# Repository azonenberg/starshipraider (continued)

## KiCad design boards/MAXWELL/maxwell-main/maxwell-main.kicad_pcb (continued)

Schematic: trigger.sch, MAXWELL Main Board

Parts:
C203: 1 uF; EIA_0603_CAP_NOSILK
C205, C206, C207, C208, C209, C210: 4.7 uF; EIA_0603_CAP_NOSILK
C211, C212, C213, C214, C215, C216, C217, C218, C219, C220, C221, C222, C224, C225, C226, C227: 0.47 uF; EIA_0402_CAP_NOSILK
C223: 0.1 uF; EIA_0402_CAP_NOSILK
C228: 0.01 uF; EIA_0402_CAP_NOSILK
J12, J13, J14, J21, J22, J23, J25: 901-10511-3; CONN_SMA_EDGE_AMPHENOL_901_10511_3
R70, R71, R72: PAT1220-C-6DB-T5; EIA_0805_PI_ATTENUATOR
R73, R74, R75: 4.99K; EIA_0402_RES_NOSILK
R77, R78, R79, R80, R81, R82: 10K; EIA_0402_RES_NOSILK
R90, R91, R93: 49.9; EIA_0402_RES_NOSILK
R125, R126, R127, R128, R129, R130: 62; EIA_0402_RES_NOSILK
R133, R134, R135, R136, R137, R138: 240; EIA_0402_RES_NOSILK
TP45, TP46, TP47, TP48: TESTCLIP; TESTPOINT_SMT_KEYSTONE_5016
U37, U38: LMH7322; QFN_24_0.5MM_4x4MM
U40: SY89835U; DFN_8_0.5MM_2x2MM
U41, U42, U43, U44, U85: RCLAMP0542T; DFN_6_0.5MM_1.6x1.0MM

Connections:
/2V5: C207.1, C210.1, C213.1, C214.1, C217.1, C218.1, C221.1, C222.1, C223.1, C226.1, C227.1, C228.1, R78.1, R80.1, R82.1, R133.1, R134.1, R135.1, R136.1, R137.1, R138.1, TP48.1, U37.1 (VCCO), U37.18 (VCCO), U37.21 (VCCO), U37.22 (VCCO), U38.1 (VCCO), U38.22 (VCCO), U40.1 (VCC); also elsewhere on the board
/5V0: C205.1, C208.1, C211.1, C215.1, C219.1, C224.1, TP46.1, U37.5 (VCCI), U37.14 (VCCI), U38.5 (VCCI); also elsewhere on the board
/5V0_N: C206.1, C209.1, C212.1, C216.1, C220.1, C225.1, R77.1, R79.1, R81.1, TP47.1, U37.4 (VSS), U37.15 (VSS), U37.PAD, U38.4 (VSS), U38.PAD; also elsewhere on the board
/Clocking/EXT_TRIG_1_N: U40.7 (Q0_N); also elsewhere on the board
/Clocking/EXT_TRIG_1_P: U40.8 (Q0_P); also elsewhere on the board
/Clocking/EXT_TRIG_2_N: U40.5 (Q1_N); also elsewhere on the board
/Clocking/EXT_TRIG_2_P: U40.6 (Q1_P); also elsewhere on the board
/Clocking/REF_IN_N: R128.1, R136.2, U38.24 (Q_N); also elsewhere on the board
/Clocking/REF_IN_P: R127.1, R135.2, U38.23 (Q_P); also elsewhere on the board
/Clocking/REF_OUT: J23.1 (In), U44.1 (LINE_1), U44.6 (NC_1); also elsewhere on the board
/Clocking/REF_OUT_N: J21.1 (In), U43.1 (LINE_1), U43.6 (NC_1); also elsewhere on the board
/Clocking/REF_OUT_P: J22.1 (In), U43.2 (LINE_2), U43.5 (NC_2); also elsewhere on the board
/Clocking/TRIG_OUT_MUX_P: J25.1 (In), U85.1 (LINE_1), U85.6 (NC_1); also elsewhere on the board
/Clocking/Trigger and Reference Inputs/PPS_IN: J14.1 (In), R72.1 (RF_IN)
/Clocking/Trigger and Reference Inputs/PPS_IN_ATTEN: R72.2 (RF_OUT), R91.1, U37.8 (IN_P), U42.1 (LINE_1), U42.6 (NC_1)
/Clocking/Trigger and Reference Inputs/REFCLK_IN: J13.1 (In), R71.1 (RF_IN)
/Clocking/Trigger and Reference Inputs/REF_IN_AC: C203.1, R93.1, U38.8 (IN_P)
/Clocking/Trigger and Reference Inputs/REF_IN_ATTEN: C203.2, R71.2 (RF_OUT), U41.2 (LINE_2), U41.5 (NC_2)
/Clocking/Trigger and Reference Inputs/TRIG_IN: J12.1 (In), R70.1 (RF_IN)
/Clocking/Trigger and Reference Inputs/TRIG_IN_ATTEN: R70.2 (RF_OUT), R90.1, U37.11 (IN_P), U42.2 (LINE_2), U42.5 (NC_2)
/Clocking/Trigger and Reference Inputs/TRIG_IN_N: R126.1, R134.2, U37.19 (Q_N), U40.3 (IN_N)
/Clocking/Trigger and Reference Inputs/TRIG_IN_P: R125.1, R133.2, U37.20 (Q_P), U40.2 (IN_P)
/GND: C205.2, C206.2, C207.2, C208.2, C209.2, C210.2, C211.2, C212.2, C213.2, C214.2, C215.2, C216.2, C217.2, C218.2, C219.2, C220.2, C221.2, C222.2, C223.2, C224.2, C225.2, C226.2, C227.2, C228.2, J12.2 (Ext), J13.2 (Ext), J14.2 (Ext), J21.2 (Ext), J22.2 (Ext), J23.2 (Ext), J25.2 (Ext), R70.3 (GND), R71.3 (GND), R72.3 (GND), R90.2, R91.2, R93.2, R125.2, R126.2, R127.2, R128.2, R129.2, R130.2, TP45.1, U37.7 (IN_N), U37.12 (IN_N), U38.7 (IN_N), U40.4 (GND), U40.PAD (GND), U41.3 (Gnd), U41.4 (Gnd), U42.3 (Gnd), U42.4 (Gnd), U43.3 (Gnd), U43.4 (Gnd), U44.3 (Gnd), U44.4 (Gnd), U85.3 (Gnd), U85.4 (Gnd); also elsewhere on the board
/PPS_IN_N: R130.1, R138.2, U37.24 (Q_N); also elsewhere on the board
/PPS_IN_P: R129.1, R137.2, U37.23 (Q_P); also elsewhere on the board
unnamed: R73.1, U37.13 (RHYS)
unnamed: R73.2, U37.10 (RHREF)
unnamed: R74.1, U38.6 (RHYS)
unnamed: R74.2, U38.9 (RHREF)
unnamed: R75.1, U37.6 (RHYS)
unnamed: R75.2, U37.9 (RHREF)
unnamed: R77.2, U37.17 (LE_P)
unnamed: R78.2, U37.16 (LE_N)
unnamed: R79.2, U38.2 (LE_P)
unnamed: R80.2, U38.3 (LE_N)
unnamed: R81.2, U37.2 (LE_P)
unnamed: R82.2, U37.3 (LE_N)

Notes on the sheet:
PECL load resistors
Attenuator power limit is +21.25 dBm or ~~7V p-p Rate the input for +20 dBm max to provide some safety margin. Comparator starts slowing down around +/- 20 mV overdrive. This is +/- 40 mV before the attenuator or about -18 dBm.
20 mV hysteresis
Comparator decoupling

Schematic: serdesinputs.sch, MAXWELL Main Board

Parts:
C65, C66, C67, C68, C81, C82, C89, C90, C355, C356, C357, C358, C365, C366, C367, C368: 1 uF; EIA_0603_CAP_NOSILK
C69, C70, C75, C76, C85, C86, C93, C94, C99, C100, C109, C110, C269, C270: 0.1 uF; EIA_0402_CAP_NOSILK
C71, C72, C73, C74, C77, C78, C79, C80, C83, C84, C87, C88, C91, C92, C95, C96, C107, C108, C111, C112, C351, C352, C353, C354, C359, C360, C361, C362, C363, C364, C369, C370, C371, C372, C373, C374: 0.01 uF; EIA_0402_CAP_NOSILK
C440, C441, C442, C443, C444, C445, C446, C447: 0.47 uF; EIA_0402_CAP_NOSILK
R85, R86, R87, R88: 220; EIA_0402_RES_NOSILK
R142, R145, R148, R183: DNP; EIA_0402_RES_NOSILK
R143, R144, R146, R147, R149, R182, R184, R185: 750; EIA_0402_RES_NOSILK
U2: XC7K160T-2FFG676C; BGA_676_27x27_FULLARRAY_1MM_FFG676
U30, U31, U32, U33: SY56017R; QFN_16_0.5MM_3x3MM
U48, U49, U50, U51: ADCMP582; QFN_16_0.5MM_3x3MM

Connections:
/0V5: C68.1, C78.1, C90.1, C352.1, C358.1, C362.1, C368.1, C372.1, C440.1, C441.1, C444.1, C445.1, U30.2 (VT0), U31.2 (VT0), U32.2 (VT0), U33.2 (VT0), U48.1 (VT_P), U48.4 (VT_N), U48.8 (VCCO_VTT), U49.1 (VT_P), U49.4 (VT_N), U49.8 (VCCO_VTT), U50.1 (VT_P), U50.4 (VT_N), U50.8 (VCCO_VTT), U51.1 (VT_P), U51.4 (VT_N), U51.8 (VCCO_VTT); also elsewhere on the board
/1V2: C75.1, C76.1, C83.1, C84.1, C85.1, C86.1, C87.1, C88.1, C99.1, C100.1, C107.1, C108.1, C109.1, C110.1, C111.1, C112.1, U30.8 (VCCO), U30.13 (VCCO), U31.8 (VCCO), U31.13 (VCCO), U32.8 (VCCO), U32.13 (VCCO), U33.8 (VCCO), U33.13 (VCCO); also elsewhere on the board
/2V5: C67.1, C69.1, C70.1, C71.1, C72.1, C77.1, C80.1, C89.1, C93.1, C94.1, C95.1, C96.1, C351.1, C354.1, C357.1, C361.1, C364.1, C367.1, C371.1, C374.1, C442.1, C443.1, C446.1, C447.1, R85.1, R87.1, R143.1, R146.1, R149.1, R184.1, U30.3 (VT1), U30.7 (VCC), U31.3 (VT1), U31.7 (VCC), U32.3 (VT1), U32.7 (VCC), U33.3 (VT1), U33.7 (VCC), U48.9 (VCCO), U48.12 (VCCO), U49.9 (VCCO), U49.12 (VCCO), U50.9 (VCCO), U50.12 (VCCO), U51.9 (VCCO), U51.12 (VCCO); also elsewhere on the board
/5V0: C65.1, C73.1, C79.1, C81.1, C91.1, C353.1, C355.1, C359.1, C363.1, C365.1, C369.1, C373.1, U48.5 (VCCI), U48.16 (VCCI), U49.5 (VCCI), U49.16 (VCCI), U50.5 (VCCI), U50.16 (VCCI), U51.5 (VCCI), U51.16 (VCCI); also elsewhere on the board
/5V0_N: C66.1, C74.1, C82.1, C92.1, C356.1, C360.1, C366.1, C370.1, R142.1, R145.1, R148.1, R183.1, U48.13 (VEE), U49.13 (VEE), U50.13 (VEE), U51.13 (VEE); also elsewhere on the board
/Clocking/EXT_TRIG_1_N: U30.5 (IN1_N); also elsewhere on the board
/Clocking/EXT_TRIG_1_P: U30.4 (IN1_P); also elsewhere on the board
/Clocking/GTX_TRIG_OUT_N: U2.F1 (MGTXTXN0_116); also elsewhere on the board
/Clocking/GTX_TRIG_OUT_P: U2.F2 (MGTXTXP0_116); also elsewhere on the board
/Clocking/LA_REFCLK_N: C270.2; also elsewhere on the board
/Clocking/LA_REFCLK_P: C269.2; also elsewhere on the board
/Clocking/SYNC_CLK_1_N: U31.5 (IN1_N); also elsewhere on the board
/Clocking/SYNC_CLK_1_P: U31.4 (IN1_P); also elsewhere on the board
/GND: C65.2, C66.2, C67.2, C68.2, C69.2, C70.2, C71.2, C72.2, C73.2, C74.2, C75.2, C76.2, C77.2, C78.2, C79.2, C80.2, C81.2, C82.2, C83.2, C84.2, C85.2, C86.2, C87.2, C88.2, C89.2, C90.2, C91.2, C92.2, C93.2, C94.2, C95.2, C96.2, C99.2, C100.2, C107.2, C108.2, C109.2, C110.2, C111.2, C112.2, C351.2, C352.2, C353.2, C354.2, C355.2, C356.2, C357.2, C358.2, C359.2, C360.2, C361.2, C362.2, C363.2, C364.2, C365.2, C366.2, C367.2, C368.2, C369.2, C370.2, C371.2, C372.2, C373.2, C374.2, C440.2, C441.2, C442.2, C443.2, C444.2, C445.2, C446.2, C447.2, R86.1, R88.1, R144.1, R147.1, R182.1, R185.1, U30.14 (GND), U30.PAD (GND), U31.14 (GND), U31.PAD (GND), U32.14 (GND), U32.PAD (GND), U33.14 (GND), U33.PAD (GND), U48.15 (GND), U49.15 (GND), U50.15 (GND), U51.15 (GND); also elsewhere on the board
/Inputs/Right Pods/MUX0_EQ: U30.6 (EQ); also elsewhere on the board
/Inputs/Right Pods/MUX0_SEL: U30.15 (SEL); also elsewhere on the board
/Inputs/Right Pods/MUX1_EQ: U31.6 (EQ); also elsewhere on the board
/Inputs/Right Pods/MUX1_SEL: U31.15 (SEL); also elsewhere on the board
/Inputs/Right Pods/MUX2_EQ: U32.6 (EQ); also elsewhere on the board
/Inputs/Right Pods/MUX2_SEL: U32.15 (SEL); also elsewhere on the board
/Inputs/Right Pods/MUX3_EQ: U33.6 (EQ); also elsewhere on the board
/Inputs/Right Pods/MUX3_SEL: U33.15 (SEL); also elsewhere on the board
/Inputs/Right Pods/POD11_D4_N: U48.2 (VIN_P); also elsewhere on the board
/Inputs/Right Pods/POD11_D4_P: U48.3 (VIN_N); also elsewhere on the board
/Inputs/Right Pods/POD11_D5_N: U49.2 (VIN_P); also elsewhere on the board
/Inputs/Right Pods/POD11_D5_P: U49.3 (VIN_N); also elsewhere on the board
/Inputs/Right Pods/POD11_D6_N: U50.2 (VIN_P); also elsewhere on the board
/Inputs/Right Pods/POD11_D6_P: U50.3 (VIN_N); also elsewhere on the board
/Inputs/Right Pods/POD11_D7_N: U51.2 (VIN_P); also elsewhere on the board
/Inputs/Right Pods/POD11_D7_P: U51.3 (VIN_N); also elsewhere on the board
/Inputs/Right Pods/SERDES inputs/CH0_N: U2.G3 (MGTXRXN0_116), U30.10 (Q_N)
/Inputs/Right Pods/SERDES inputs/CH0_P: U2.G4 (MGTXRXP0_116), U30.11 (Q_P)
/Inputs/Right Pods/SERDES inputs/CH1_N: U2.E3 (MGTXRXN1_116), U31.10 (Q_N)
/Inputs/Right Pods/SERDES inputs/CH1_P: U2.E4 (MGTXRXP1_116), U31.11 (Q_P)
/Inputs/Right Pods/SERDES inputs/CH2_N: U2.C3 (MGTXRXN2_116), U32.10 (Q_N)
/Inputs/Right Pods/SERDES inputs/CH2_P: U2.C4 (MGTXRXP2_116), U32.11 (Q_P)
/Inputs/Right Pods/SERDES inputs/CH3_N: U2.B5 (MGTXRXN3_116), U33.10 (Q_N)
/Inputs/Right Pods/SERDES inputs/CH3_P: U2.B6 (MGTXRXP3_116), U33.11 (Q_P)
/Inputs/Right Pods/SERDES inputs/IN0_BUF_N: U30.1 (IN0_N), U48.11 (Q_P)
/Inputs/Right Pods/SERDES inputs/IN0_BUF_P: U30.16 (IN0_P), U48.10 (Q_N)
/Inputs/Right Pods/SERDES inputs/IN1_BUF_N: U31.1 (IN0_N), U49.11 (Q_P)
/Inputs/Right Pods/SERDES inputs/IN1_BUF_P: U31.16 (IN0_P), U49.10 (Q_N)
/Inputs/Right Pods/SERDES inputs/IN2_BUF_N: U32.1 (IN0_N), U50.11 (Q_P)
/Inputs/Right Pods/SERDES inputs/IN2_BUF_P: U32.16 (IN0_P), U50.10 (Q_N)
/Inputs/Right Pods/SERDES inputs/IN3_BUF_N: U33.1 (IN0_N), U51.11 (Q_P)
/Inputs/Right Pods/SERDES inputs/IN3_BUF_P: U33.16 (IN0_P), U51.10 (Q_N)
/Inputs/Right Pods/SERDES inputs/REFCLK_AC_N: C270.1, U2.D5 (MGTREFCLK0N_116)
/Inputs/Right Pods/SERDES inputs/REFCLK_AC_P: C269.1, U2.D6 (MGTREFCLK0P_116)
/Inputs/Right Pods/SERDES inputs/UNUSED1_N: R86.2, U32.5 (IN1_N)
/Inputs/Right Pods/SERDES inputs/UNUSED1_P: R85.2, U32.4 (IN1_P)
/Inputs/Right Pods/SERDES inputs/UNUSED2_N: R88.2, U33.5 (IN1_N)
/Inputs/Right Pods/SERDES inputs/UNUSED2_P: R87.2, U33.4 (IN1_P)
unnamed: R142.2, U48.14 (VHYS)
unnamed: R143.2, U48.7 (LE_P)
unnamed: R144.2, U48.6 (LE_N)
unnamed: R145.2, U49.14 (VHYS)
unnamed: R146.2, U49.7 (LE_P)
unnamed: R147.2, U49.6 (LE_N)
unnamed: R148.2, U50.14 (VHYS)
unnamed: R149.2, U50.7 (LE_P)
unnamed: R182.2, U50.6 (LE_N)
unnamed: R183.2, U51.14 (VHYS)
unnamed: R184.2, U51.7 (LE_P)
unnamed: R185.2, U51.6 (LE_N)

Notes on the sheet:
Tie unused inputs to constant value so they don't oscillate
SY56017 @ VCCO=1V2 Output swing 780 mV differential below 1V2 Input 400 - 2000 mV Input to Vt max 1280 mV GTX: inputs terminated with 50 ohms per leg to Avtt SE input range -200 to +1200 mV Input voltage 150 to 1250 differential

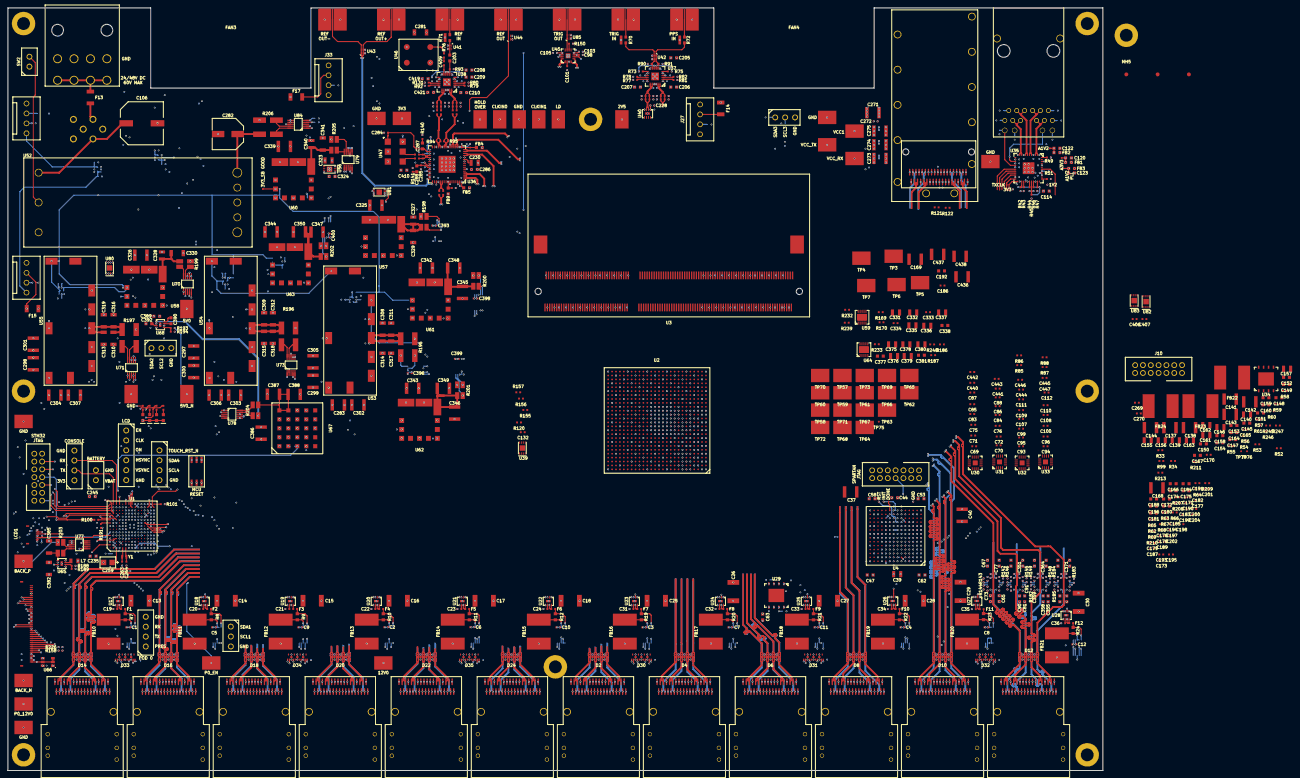
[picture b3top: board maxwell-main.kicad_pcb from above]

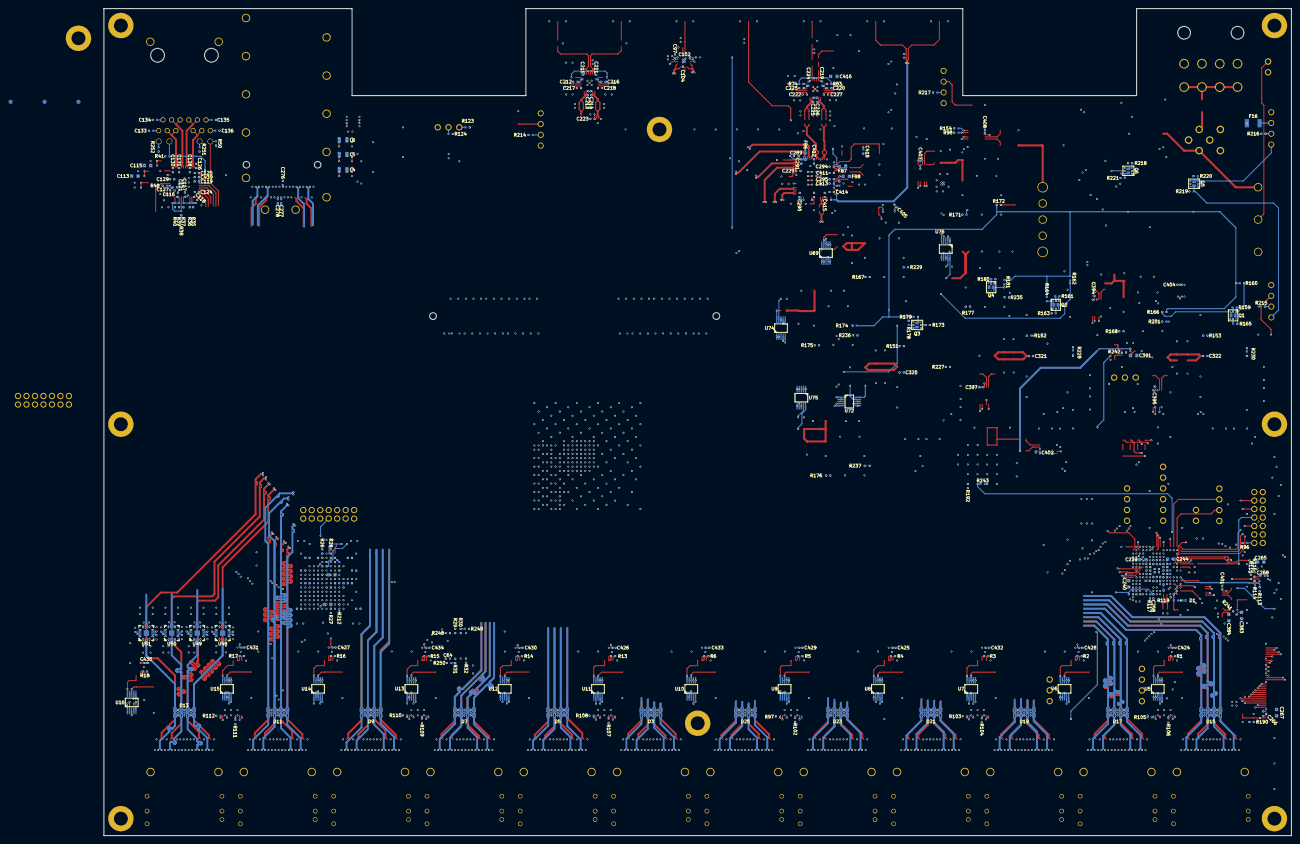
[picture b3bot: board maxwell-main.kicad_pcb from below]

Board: 8 copper layers, 280.0 x 195.0 mm, 996 parts (290 on the bottom side), 921 nets.

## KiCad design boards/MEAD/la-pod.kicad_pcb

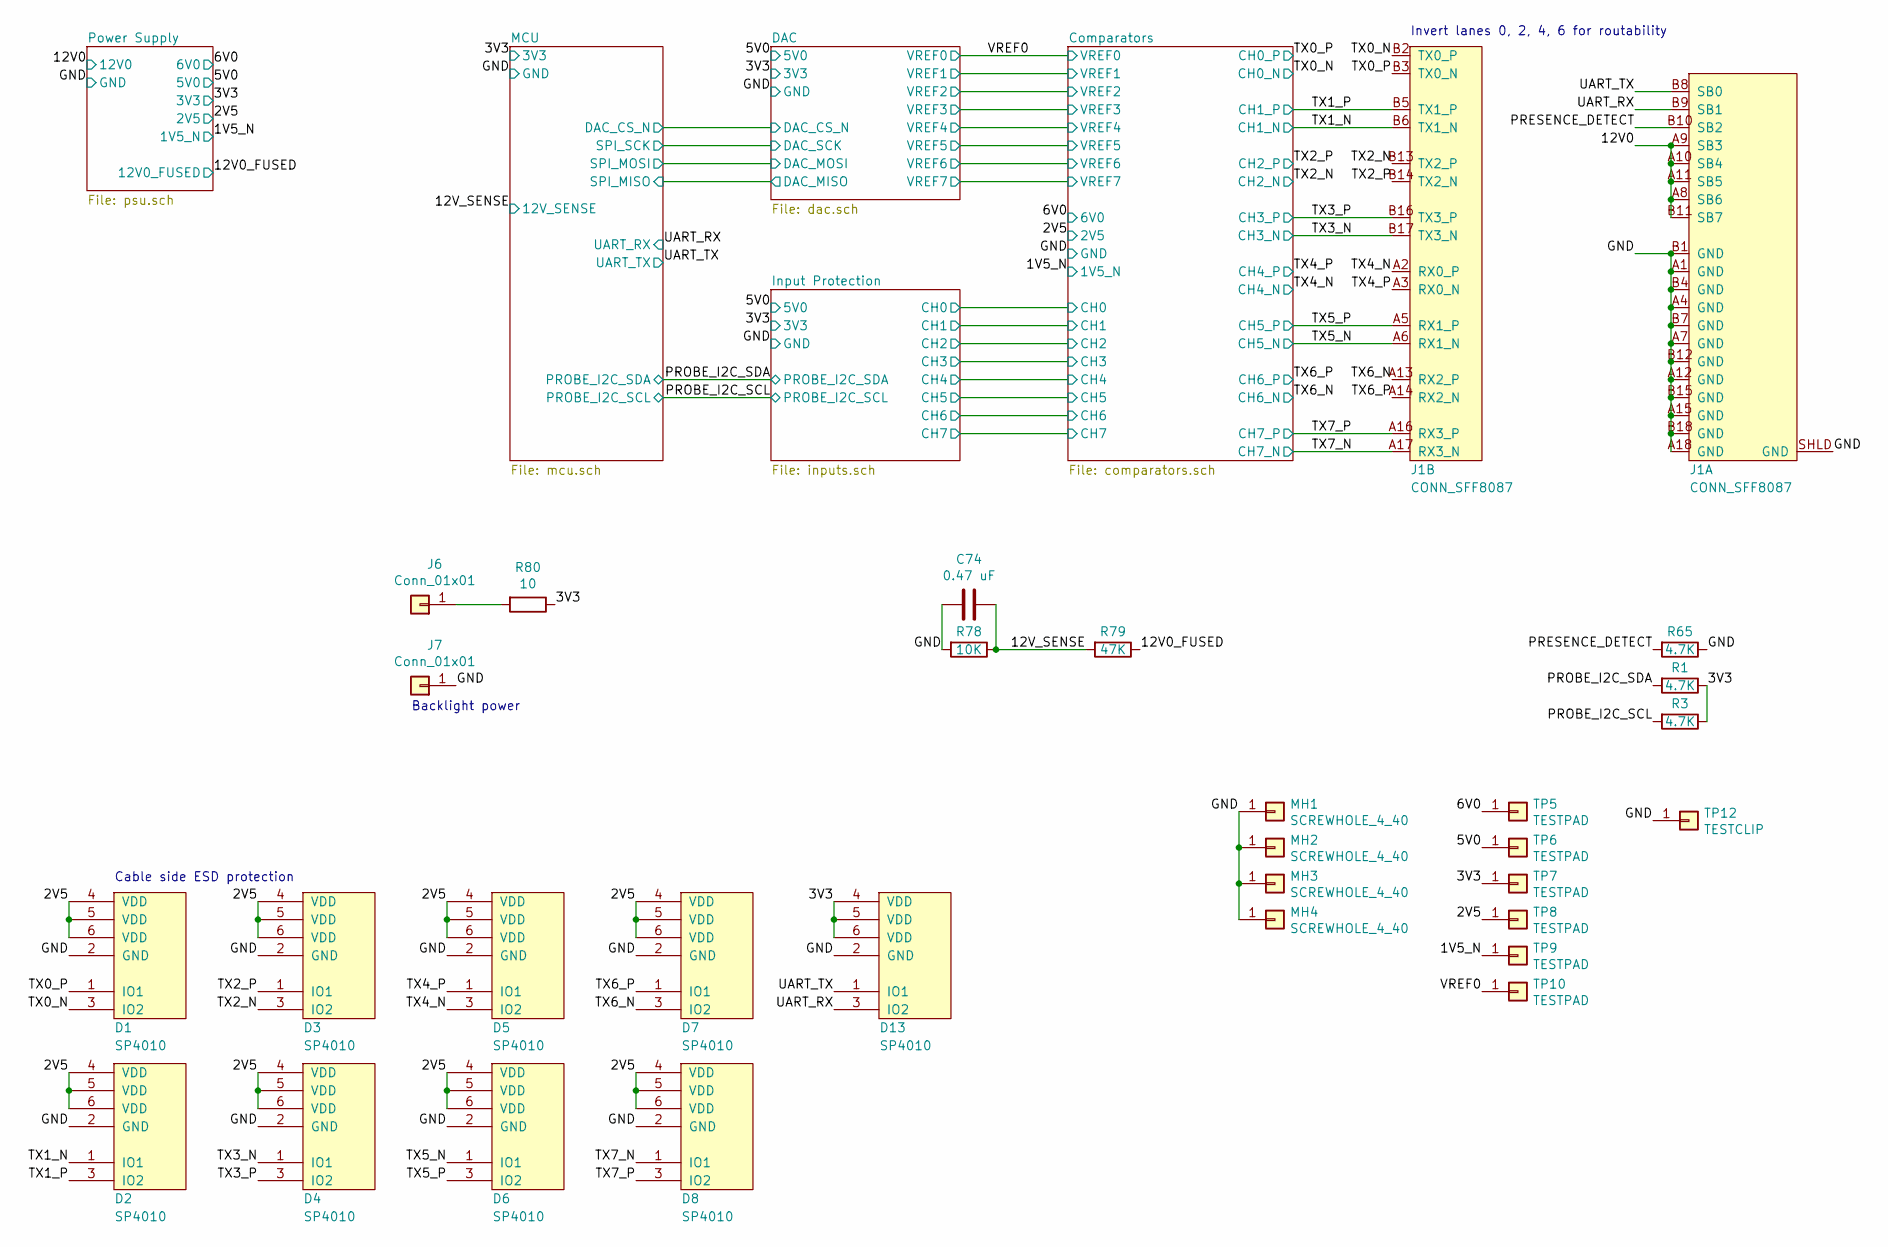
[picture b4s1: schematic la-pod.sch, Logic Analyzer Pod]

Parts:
C74: 0.47 uF; EIA_0402_CAP_NOSILK
D1, D2, D3, D4, D5, D6, D7, D8, D13: SP4010; SOT23_6
J1: CONN_SFF8087; CONN_SFF8087_MOLEX_75783-0140
J6, J7: Conn_01x01; CONN_HEADER_2.54MM_1x1
MH1, MH2, MH3, MH4: SCREWHOLE_4_40; MECHANICAL_CLEARANCEHOLE_4_40
R1, R3, R65: 4.7K; EIA_0402_RES_NOSILK
R78: 10K; EIA_0402_RES_NOSILK
R79: 47K; EIA_0402_RES_NOSILK
R80: 10; EIA_0805_CAP_NOSILK
TP5, TP6, TP7, TP8, TP9, TP10: TESTPAD; TESTPOINT_SMT_0.5MM
TP12: TESTCLIP; TESTPOINT_SMT_KEYSTONE_5016

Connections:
/1V5_N: TP9.1; also elsewhere on the board
/2V5: D1.4 (VDD), D1.5 (VDD), D1.6 (VDD), D2.4 (VDD), D2.5 (VDD), D2.6 (VDD), D3.4 (VDD), D3.5 (VDD), D3.6 (VDD), D4.4 (VDD), D4.5 (VDD), D4.6 (VDD), D5.4 (VDD), D5.5 (VDD), D5.6 (VDD), D6.4 (VDD), D6.5 (VDD), D6.6 (VDD), D7.4 (VDD), D7.5 (VDD), D7.6 (VDD), D8.4 (VDD), D8.5 (VDD), D8.6 (VDD), TP8.1; also elsewhere on the board
/3V3: D13.4 (VDD), D13.5 (VDD), D13.6 (VDD), R1.1, R3.1, R80.1, TP7.1; also elsewhere on the board
/5V0: TP6.1; also elsewhere on the board
/6V0: TP5.1; also elsewhere on the board
/12V0: J1.A8 (SB6), J1.A9 (SB3), J1.A10 (SB4), J1.A11 (SB5), J1.B11 (SB7); also elsewhere on the board
/12V0_FUSED: R79.1; also elsewhere on the board
/12V_SENSE: C74.1, R78.1, R79.2; also elsewhere on the board
/GND: C74.2, D1.2 (GND), D2.2 (GND), D3.2 (GND), D4.2 (GND), D5.2 (GND), D6.2 (GND), D7.2 (GND), D8.2 (GND), D13.2 (GND), J1.A1 (GND), J1.A4 (GND), J1.A7 (GND), J1.A12 (GND), J1.A15 (GND), J1.A18 (GND), J1.B1 (GND), J1.B4 (GND), J1.B7 (GND), J1.B12 (GND), J1.B15 (GND), J1.B18 (GND), J1.SHLD (GND), J7.1, MH1.1, MH2.1, MH3.1, MH4.1, R65.1, R78.2, TP12.1; also elsewhere on the board
/PRESENCE_DETECT: J1.B10 (SB2), R65.2
/PROBE_I2C_SCL: R3.2; also elsewhere on the board
/PROBE_I2C_SDA: R1.2; also elsewhere on the board
/TX0_N: D1.3 (IO2), J1.B2 (TX0_P); also elsewhere on the board
/TX0_P: D1.1 (IO1), J1.B3 (TX0_N); also elsewhere on the board
/TX1_N: D2.1 (IO1), J1.B6 (TX1_N); also elsewhere on the board
/TX1_P: D2.3 (IO2), J1.B5 (TX1_P); also elsewhere on the board
/TX2_N: D3.3 (IO2), J1.B13 (TX2_P); also elsewhere on the board
/TX2_P: D3.1 (IO1), J1.B14 (TX2_N); also elsewhere on the board
/TX3_N: D4.1 (IO1), J1.B17 (TX3_N); also elsewhere on the board
/TX3_P: D4.3 (IO2), J1.B16 (TX3_P); also elsewhere on the board
/TX4_N: D5.3 (IO2), J1.A2 (RX0_P); also elsewhere on the board
/TX4_P: D5.1 (IO1), J1.A3 (RX0_N); also elsewhere on the board
/TX5_N: D6.1 (IO1), J1.A6 (RX1_N); also elsewhere on the board
/TX5_P: D6.3 (IO2), J1.A5 (RX1_P); also elsewhere on the board
/TX6_N: D7.3 (IO2), J1.A13 (RX2_P); also elsewhere on the board
/TX6_P: D7.1 (IO1), J1.A14 (RX2_N); also elsewhere on the board
/TX7_N: D8.1 (IO1), J1.A17 (RX3_N); also elsewhere on the board
/TX7_P: D8.3 (IO2), J1.A16 (RX3_P); also elsewhere on the board
/UART_RX: D13.3 (IO2), J1.B9 (SB1); also elsewhere on the board
/UART_TX: D13.1 (IO1), J1.B8 (SB0); also elsewhere on the board
/VREF0: TP10.1; also elsewhere on the board
unnamed: J6.1, R80.2

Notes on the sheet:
Cable side ESD protection
Invert lanes 0, 2, 4, 6 for routability
Backlight power

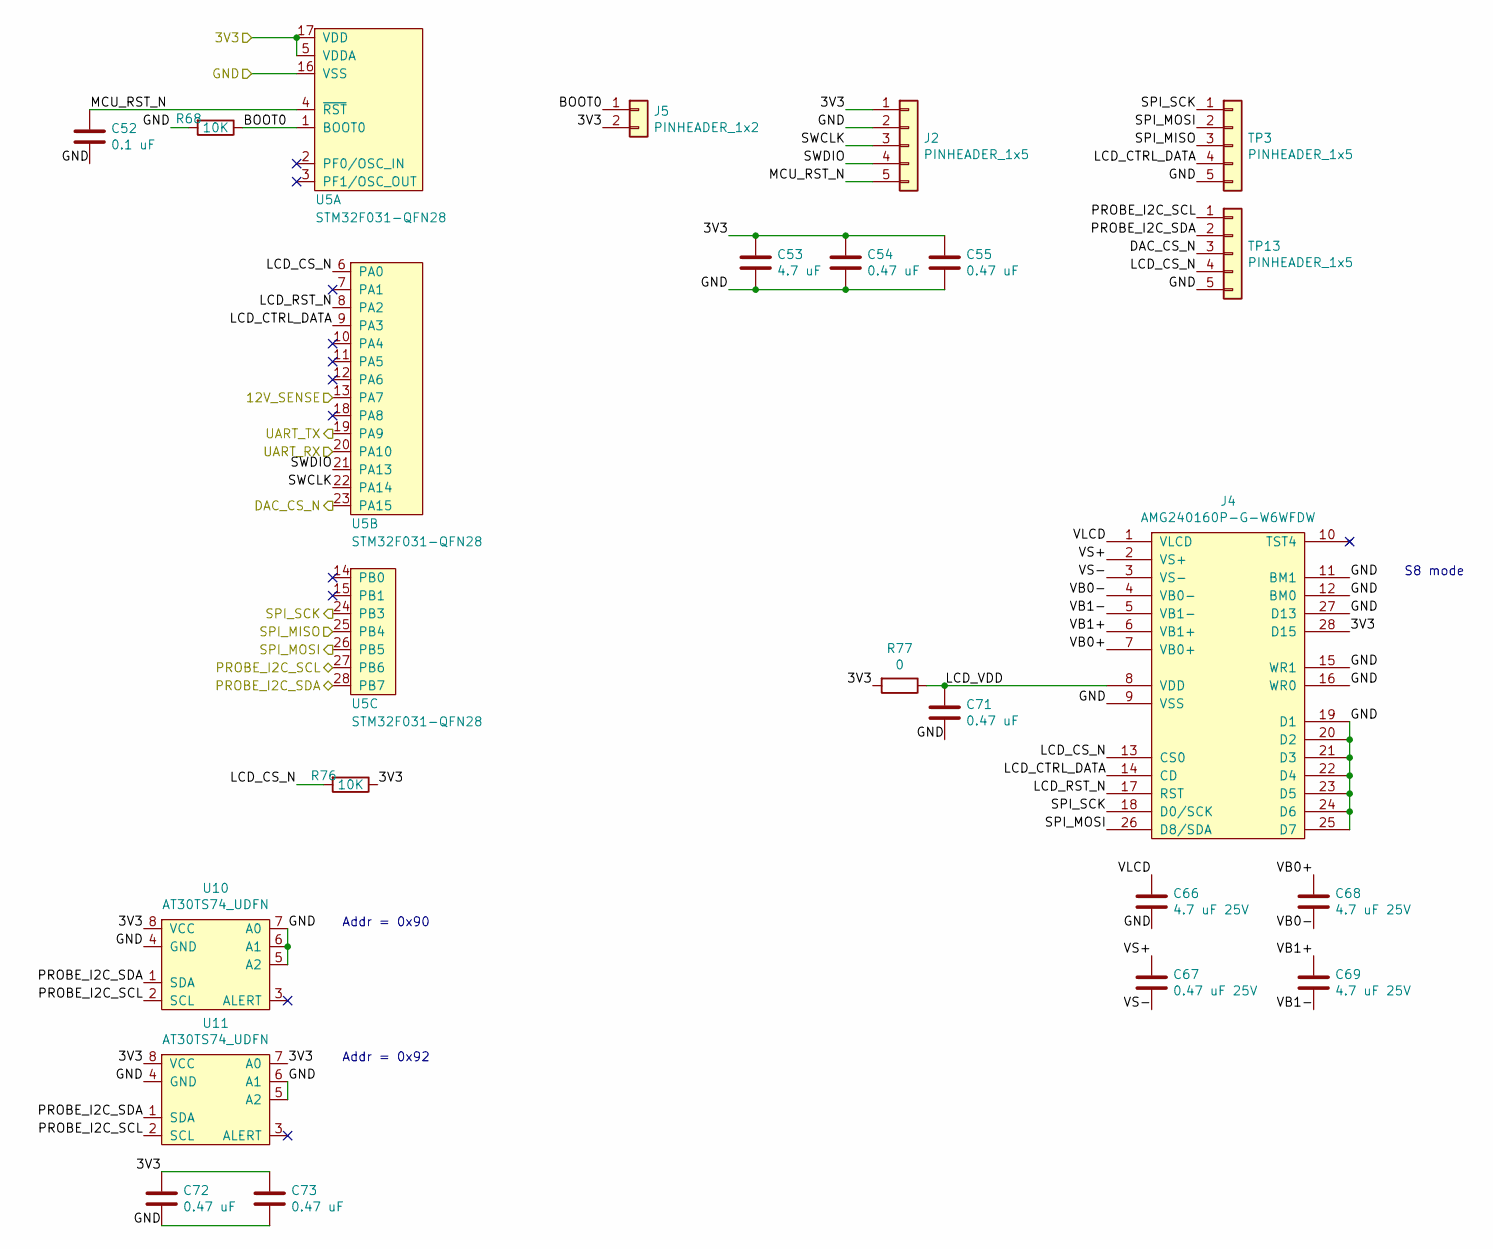
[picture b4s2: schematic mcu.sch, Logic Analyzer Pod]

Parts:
C52: 0.1 uF; EIA_0402_CAP_NOSILK
C53: 4.7 uF; EIA_0603_CAP_NOSILK
C54, C55, C71, C72, C73: 0.47 uF; EIA_0402_CAP_NOSILK
C66, C68, C69: 4.7 uF 25V; EIA_0805_CAP_NOSILK
C67: 0.47 uF 25V; EIA_0402_CAP_NOSILK
J2: PINHEADER_1x5; CONN_HEADER_2.54MM_1x5
J4: AMG240160P-G-W6WFDW; CONN_FFC_0.5MM_1x28_MOLEX_0524352871
J5: PINHEADER_1x2; CONN_HEADER_2.54MM_1x2
R68, R76: 10K; EIA_0402_RES_NOSILK
R77: 0; EIA_0402_RES_NOSILK
TP3, TP13: PINHEADER_1x5; CONN_HEADER_2.54MM_1x5
U5: STM32F031-QFN28; QFN_28_0.5MM_4x4MM_NOPAD
U10, U11: AT30TS74_UDFN; DFN_8_0.5MM_3x3MM

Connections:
/3V3: C53.1, C54.1, C55.1, C72.1, C73.1, J2.1, J4.28 (D15), J5.2, R76.1, R77.2, U5.5 (VDDA), U5.17 (VDD), U10.8 (VCC), U11.7 (A0), U11.8 (VCC); also elsewhere on the board
/12V_SENSE: U5.13 (PA7); also elsewhere on the board
/DAC/DAC_CS_N: TP13.3, U5.23 (PA15); also elsewhere on the board
/DAC/DAC_MISO: TP3.3, U5.25 (PB4); also elsewhere on the board
/DAC/DAC_MOSI: J4.26 (D8/SDA), TP3.2, U5.26 (PB5); also elsewhere on the board
/DAC/DAC_SCK: J4.18 (D0/SCK), TP3.1, U5.24 (PB3); also elsewhere on the board
/GND: C52.2, C53.2, C54.2, C55.2, C66.2, C71.2, C72.2, C73.2, J2.2, J4.9 (VSS), J4.11 (BM1), J4.12 (BM0), J4.15 (WR1), J4.16 (WR0), J4.19 (D1), J4.20 (D2), J4.21 (D3), J4.22 (D4), J4.23 (D5), J4.24 (D6), J4.25 (D7), J4.27 (D13), R68.2, TP3.5, TP13.5, U5.16 (VSS), U10.4 (GND), U10.5 (A2), U10.6 (A1), U10.7 (A0), U11.4 (GND), U11.5 (A2), U11.6 (A1); also elsewhere on the board
/MCU/BOOT0: J5.1, R68.1, U5.1 (BOOT0)
/MCU/LCD_CS_N: J4.13 (CS0), R76.2, TP13.4, U5.6 (PA0)
/MCU/LCD_CTRL_DATA: J4.14 (CD), TP3.4, U5.9 (PA3)
/MCU/LCD_RST_N: J4.17 (RST), U5.8 (PA2)
/MCU/LCD_VDD: C71.1, J4.8 (VDD), R77.1
/MCU/MCU_RST_N: C52.1, J2.5, U5.4 (~RST)
/MCU/SWCLK: J2.3, U5.22 (PA14)
/MCU/SWDIO: J2.4, U5.21 (PA13)
/MCU/VB0+: C68.1, J4.7 (VB0+)
/MCU/VB0-: C68.2, J4.4 (VB0-)
/MCU/VB1+: C69.1, J4.6 (VB1+)
/MCU/VB1-: C69.2, J4.5 (VB1-)
/MCU/VLCD: C66.1, J4.1 (VLCD)
/MCU/VS+: C67.1, J4.2 (VS+)
/MCU/VS-: C67.2, J4.3 (VS-)
/PROBE_I2C_SCL: TP13.1, U5.27 (PB6), U10.2 (SCL), U11.2 (SCL); also elsewhere on the board
/PROBE_I2C_SDA: TP13.2, U5.28 (PB7), U10.1 (SDA), U11.1 (SDA); also elsewhere on the board
/UART_RX: U5.20 (PA10); also elsewhere on the board
/UART_TX: U5.19 (PA9); also elsewhere on the board

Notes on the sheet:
S8 mode
Addr = 0x90
Addr = 0x92

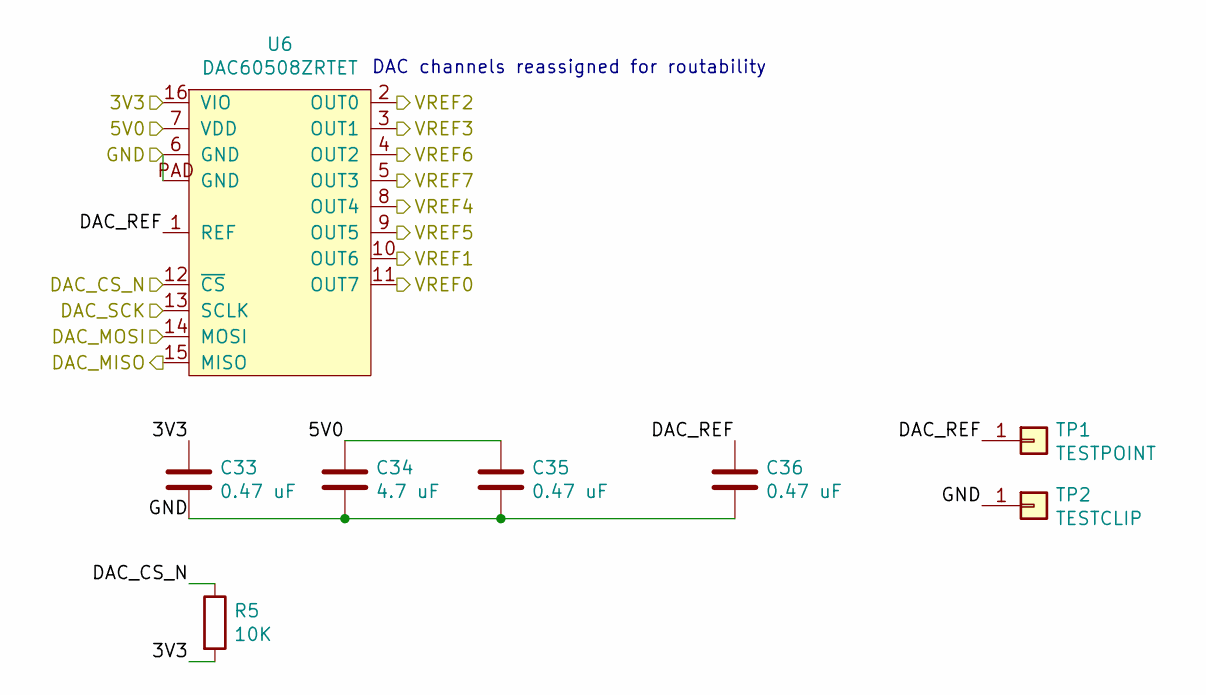
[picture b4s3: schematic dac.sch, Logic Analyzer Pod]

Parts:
C33, C35, C36: 0.47 uF; EIA_0402_CAP_NOSILK
C34: 4.7 uF; EIA_0603_CAP_NOSILK
R5: 10K; EIA_0402_RES_NOSILK
TP1: TESTPOINT; TESTPOINT_SMT_0.5MM
TP2: TESTCLIP; TESTPOINT_SMT_KEYSTONE_5016
U6: DAC60508ZRTET; QFN_16_0.5MM_3x3MM

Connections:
/3V3: C33.1, R5.2, U6.16 (VIO); also elsewhere on the board
/5V0: C34.1, C35.1, U6.7 (VDD); also elsewhere on the board
/Comparators/VREF1: U6.10 (OUT6); also elsewhere on the board
/Comparators/VREF2: U6.2 (OUT0); also elsewhere on the board
/Comparators/VREF3: U6.3 (OUT1); also elsewhere on the board
/Comparators/VREF4: U6.8 (OUT4); also elsewhere on the board
/Comparators/VREF5: U6.9 (OUT5); also elsewhere on the board
/Comparators/VREF6: U6.4 (OUT2); also elsewhere on the board
/Comparators/VREF7: U6.5 (OUT3); also elsewhere on the board
/DAC/DAC_CS_N: R5.1, U6.12 (~CS); also elsewhere on the board
/DAC/DAC_MISO: U6.15 (MISO); also elsewhere on the board
/DAC/DAC_MOSI: U6.14 (MOSI); also elsewhere on the board
/DAC/DAC_REF: C36.1, TP1.1, U6.1 (REF)
/DAC/DAC_SCK: U6.13 (SCLK); also elsewhere on the board
/GND: C33.2, C34.2, C35.2, C36.2, TP2.1, U6.6 (GND), U6.PAD (GND); also elsewhere on the board
/VREF0: U6.11 (OUT7); also elsewhere on the board

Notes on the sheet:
DAC channels reassigned for routability

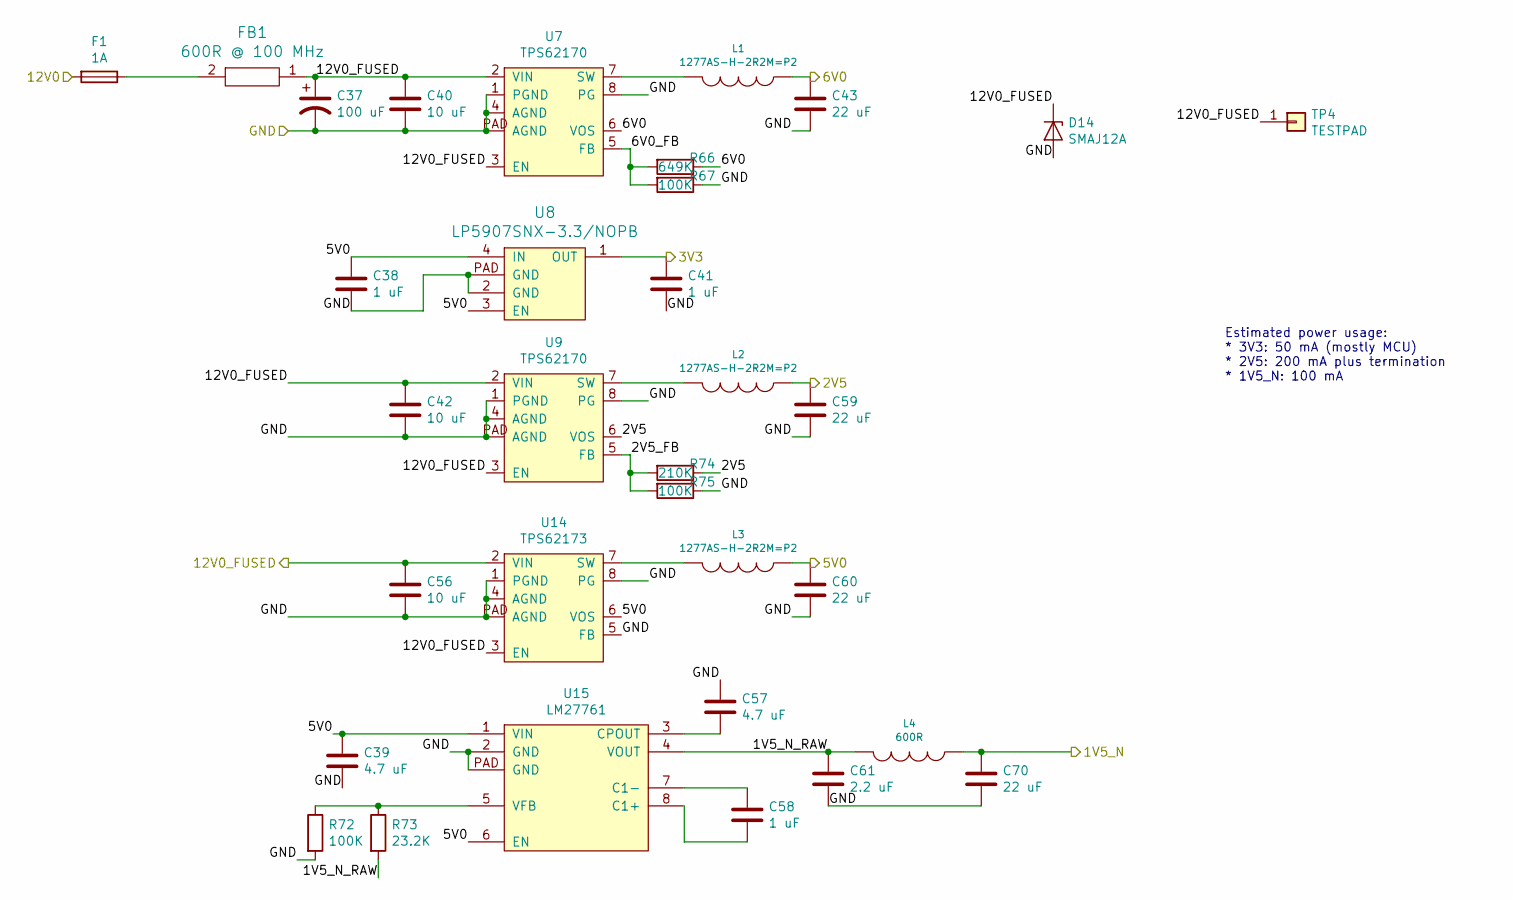
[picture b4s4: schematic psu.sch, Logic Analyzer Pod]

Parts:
C37: 100 uF; CAP_AL_6.3MM_SMT
C38, C41, C58: 1 uF; EIA_0603_CAP_NOSILK
C39, C57: 4.7 uF; EIA_0603_CAP_NOSILK
C40, C42, C56: 10 uF; EIA_1210_CAP_NOSILK
C43, C60, C70: 22 uF; EIA_1210_CAP_NOSILK
C59: 22 uF; EIA_0805_CAP_NOSILK
C61: 2.2 uF; EIA_0603_CAP_NOSILK
D14: SMAJ12A; SMA
F1: 1A; EIA_0402_RES_NOSILK
FB1: 600R @ 100 MHz; EIA_0603_INDUCTOR_NOSILK
L1, L2, L3: 1277AS-H-2R2M=P2; EIA_1210_CAP_NOSILK
L4: 600R; EIA_0603_INDUCTOR_NOSILK
R66: 649K; EIA_0402_RES_NOSILK
R67, R72, R75: 100K; EIA_0402_RES_NOSILK
R73: 23.2K; EIA_0402_RES_NOSILK
R74: 210K; EIA_0402_RES_NOSILK
TP4: TESTPAD; TESTPOINT_SMT_0.5MM
U7, U9: TPS62170; DFN_8_0.5MM_2x2MM
U8: LP5907SNX-3.3/NOPB; DFN_4_0.65MM_1x1MM_TI_DQN
U14: TPS62173; DFN_8_0.5MM_2x2MM
U15: LM27761; DFN_8_0.5MM_2x2MM

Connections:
/1V5_N: C70.1, L4.1; also elsewhere on the board
/2V5: C59.1, L2.1, R74.1, U9.6 (VOS); also elsewhere on the board
/3V3: C41.1, U8.1 (OUT); also elsewhere on the board
/5V0: C38.1, C39.1, C60.1, L3.1, U8.3 (EN), U8.4 (IN), U14.6 (VOS), U15.1 (VIN), U15.6 (EN); also elsewhere on the board
/6V0: C43.1, L1.1, R66.1, U7.6 (VOS); also elsewhere on the board
/12V0: F1.2; also elsewhere on the board
/12V0_FUSED: C37.1, C40.1, C42.1, C56.1, D14.1 (K), FB1.1, TP4.1, U7.2 (VIN), U7.3 (EN), U9.2 (VIN), U9.3 (EN), U14.2 (VIN), U14.3 (EN); also elsewhere on the board
/GND: C37.2, C38.2, C39.2, C40.2, C41.2, C42.2, C43.2, C56.2, C57.1, C59.2, C60.2, C61.2, C70.2, D14.2 (A), R67.1, R72.2, R75.1, U7.1 (PGND), U7.4 (AGND), U7.8 (PG), U7.PAD (AGND), U8.2 (GND), U8.PAD (GND), U9.1 (PGND), U9.4 (AGND), U9.8 (PG), U9.PAD (AGND), U14.1 (PGND), U14.4 (AGND), U14.5 (FB), U14.8 (PG), U14.PAD (AGND), U15.2 (GND), U15.PAD (GND); also elsewhere on the board
/Power Supply/1V5_N_RAW: C61.1, L4.2, R73.2, U15.4 (VOUT)
/Power Supply/2V5_FB: R74.2, R75.2, U9.5 (FB)
/Power Supply/6V0_FB: R66.2, R67.2, U7.5 (FB)
unnamed: C57.2, U15.3 (CPOUT)
unnamed: C58.1, U15.7 (C1-)
unnamed: C58.2, U15.8 (C1+)
unnamed: F1.1, FB1.2
unnamed: L1.2, U7.7 (SW)
unnamed: L2.2, U9.7 (SW)
unnamed: L3.2, U14.7 (SW)
unnamed: R72.1, R73.1, U15.5 (VFB)

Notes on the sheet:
Estimated power usage: * 3V3: 50 mA (mostly MCU) * 2V5: 200 mA plus termination * 1V5_N: 100 mA
